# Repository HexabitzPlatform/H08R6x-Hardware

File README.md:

# H01R0x-Hardware
Hexabitz RGB LED Module Hardware Design

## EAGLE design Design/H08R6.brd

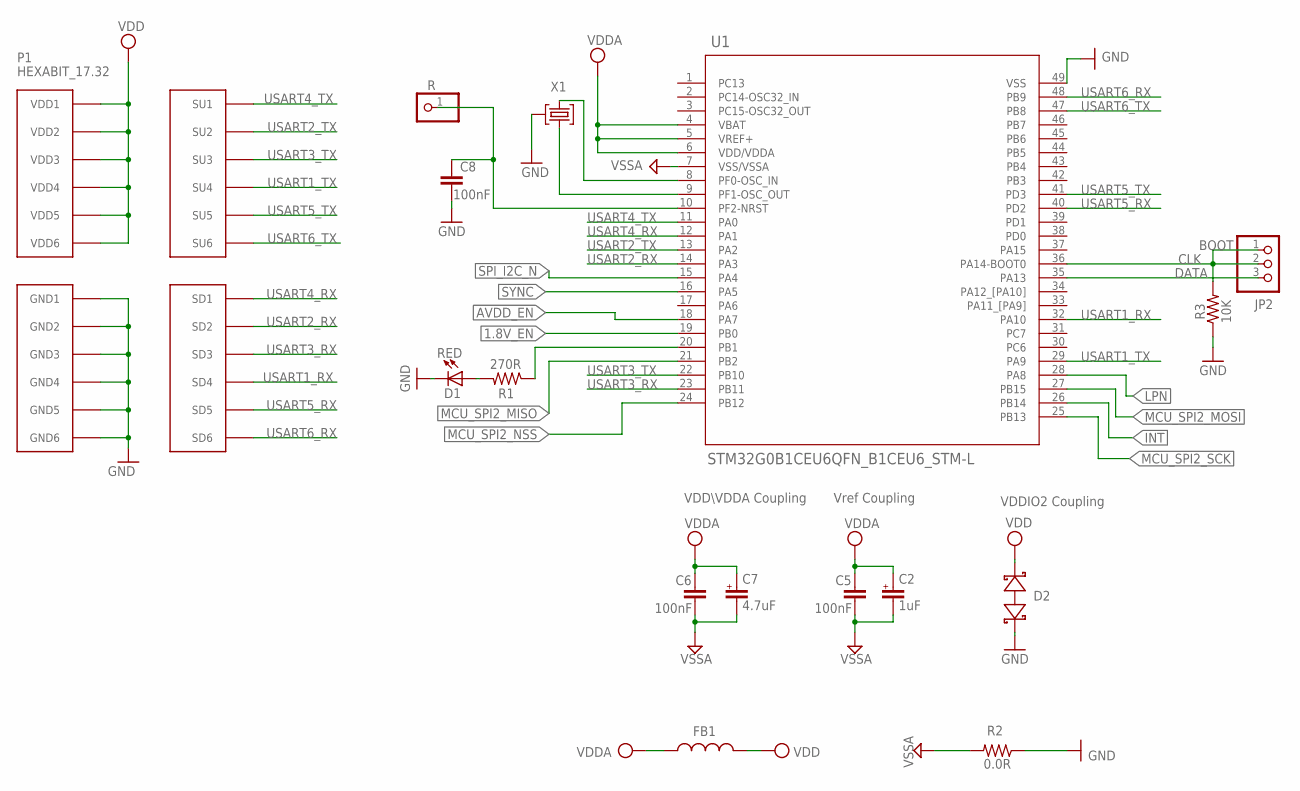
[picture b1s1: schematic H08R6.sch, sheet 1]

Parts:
C2: 1uF; C-0603-POL
C5, C6, C8: 100nF; C-0402
C7: 4.7uF; C-0603-POL
D1: RED; VLMS1300-GS08; MPN VLMS1300-GS08
D2: BOURNS_CDSOD323-T03SCBOURNS_CDSOD323-T03SC_0_0; BOURNS_CDSOD323-T03SC_0
FB1: FB-TDK_MMZ1608Y300B; MPN MMZ1608Y300B
JP2: PINHD-1X3; 1X03
P1: HEXABIT_17.32
R: R; 1X01
R1: 270R; R-0402
R2: 0.0R; R-0402; MPN RC0603JR-070RL
R3: 10K; R-0402
TRIMBLE-LOGO1: HEXA-LOGO
U1: STM32G0B1CEU6QFN_B1CEU6_STM-L; QFN_B1CEU6_STM-L
X1: XTALL_CSTCE8M00G52

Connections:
1.8V_EN: U1.19 (PB0); also elsewhere on the board
AVDD_EN: U1.18 (PA7); also elsewhere on the board
CLK: JP2.1, JP2.2, R3.2, U1.36 (PA14-BOOT0)
DATA: JP2.3, U1.35 (PA13)
GND: C8.2, D1.C, D2.2 (C), P1.PAD_PD7 (GND1), P1.PAD_PD8 (GND2), P1.PAD_PD9 (GND3), P1.PAD_PD10 (GND4), P1.PAD_PD11 (GND5), P1.PAD_PD12 (GND6), R2.1, R3.1, U1.49 (VSS), X1.P$2 (2); also elsewhere on the board
INT: U1.26 (PB14); also elsewhere on the board
LPN: U1.28 (PA8); also elsewhere on the board
MCU_SPI2_MISO: U1.21 (PB2); also elsewhere on the board
MCU_SPI2_MOSI: U1.27 (PB15); also elsewhere on the board
MCU_SPI2_NSS: U1.24 (PB12); also elsewhere on the board
MCU_SPI2_SCK: U1.25 (PB13); also elsewhere on the board
unnamed: D1.A, R1.2
unnamed: C8.1, R.1, U1.10 (PF2-NRST)
unnamed: U1.9 (PF1-OSC_OUT), X1.P$1 (1)
unnamed: U1.8 (PF0-OSC_IN), X1.P$3 (3)
unnamed: R1.1, U1.20 (PB1)
SPI_I2C_N: U1.15 (PA4); also elsewhere on the board
SYNC: U1.16 (PA5); also elsewhere on the board
USART1_RX: P1.PAD_PD4 (SD4), U1.32 (PA10)
USART1_TX: P1.PAD_PU4 (SU4), U1.29 (PA9)
USART2_RX: P1.PAD_PD2 (SD2), U1.14 (PA3)
USART2_TX: P1.PAD_PU2 (SU2), U1.13 (PA2)
USART3_RX: P1.PAD_PD3 (SD3), U1.23 (PB11)
USART3_TX: P1.PAD_PU3 (SU3), U1.22 (PB10)
USART4_RX: P1.PAD_PD1 (SD1), U1.12 (PA1)
USART4_TX: P1.PAD_PU1 (SU1), U1.11 (PA0)
USART5_RX: P1.PAD_PD5 (SD5), U1.40 (PD2)
USART5_TX: P1.PAD_PU5 (SU5), U1.41 (PD3)
USART6_RX: P1.PAD_PD6 (SD6), U1.48 (PB9)
USART6_TX: P1.PAD_PU6 (SU6), U1.47 (PB8)
VDD: D2.1 (A), FB1.2, P1.PAD_PU7 (VDD1), P1.PAD_PU8 (VDD2), P1.PAD_PU9 (VDD3), P1.PAD_PU10 (VDD4), P1.PAD_PU11 (VDD5), P1.PAD_PU12 (VDD6); also elsewhere on the board
VDDA: C2.1, C5.1, C6.1, C7.1, FB1.1, U1.4 (VBAT), U1.5 (VREF+), U1.6 (VDD/VDDA)
VSSA: C2.2, C5.2, C6.2, C7.2, R2.2, U1.7 (VSS/VSSA)

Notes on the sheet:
Vref Coupling
VDDIO2 Coupling
VDD\VDDA Coupling
BOOT

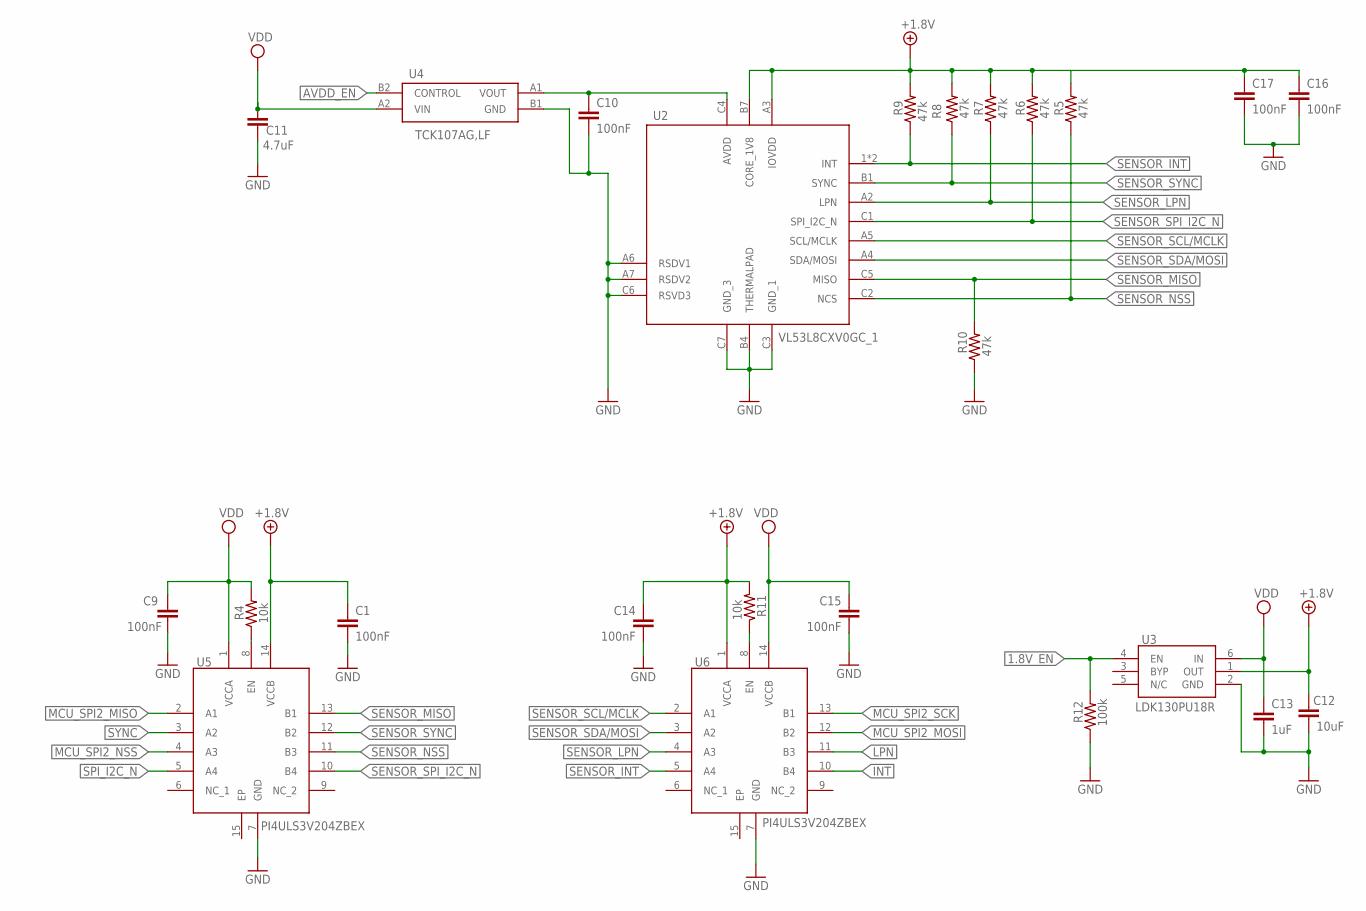
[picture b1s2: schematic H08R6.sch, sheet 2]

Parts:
C1, C9, C10, C14, C15, C16, C17: 100nF; C-0402
C11: 4.7uF; C-0603
C12: 10uF; C-0402
C13: 1uF; C-0402
R4, R11: 10k; R-0402
R5, R6, R7, R8, R9, R10: 47k; R-0402
R12: 100k; R-0402
U2: VL53L8CXV0GC_1; VL53L8CXV0GC1
U3: LDK130PU18R
U4: TCK107AG,LF; BGA4C40P2X2_79X79X59
U5, U6: PI4ULS3V204ZBEX

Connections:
1.8V_EN: R12.2, U3.4 (EN); also elsewhere on the board
+1.8V: C1.1, C12.1, C14.1, C16.1, C17.1, R5.2, R6.2, R7.2, R8.2, R9.2, R11.2, U2.A3 (IOVDD), U2.B7 (CORE_1V8), U3.1 (OUT), U5.14 (VCCB), U6.1 (VCCA)
AVDD_EN: U4.B2 (CONTROL); also elsewhere on the board
CONTROLLED_AVDD: C10.1, U2.C4 (AVDD), U4.A1 (VOUT)
GND: C1.2, C9.2, C10.2, C11.2, C12.2, C13.2, C14.2, C15.2, C16.2, C17.2, R10.1, R12.1, U2.A6 (RSDV1), U2.A7 (RSDV2), U2.B4 (THERMALPAD), U2.C3 (GND_1), U2.C6 (RSVD3), U2.C7 (GND_3), U3.2 (GND), U4.B1 (GND), U5.7 (GND), U6.7 (GND); also elsewhere on the board
INT: U6.10 (B4); also elsewhere on the board
LPN: U6.11 (B3); also elsewhere on the board
MCU_SPI2_MISO: U5.2 (A1); also elsewhere on the board
MCU_SPI2_MOSI: U6.12 (B2); also elsewhere on the board
MCU_SPI2_NSS: U5.4 (A3); also elsewhere on the board
MCU_SPI2_SCK: U6.13 (B1); also elsewhere on the board
unnamed: R4.1, U5.8 (EN)
unnamed: R11.1, U6.8 (EN)
SENSOR_INT: R9.1, U2.1 (INT), U2.A1 (INT), U6.5 (A4)
SENSOR_LPN: R7.1, U2.A2 (LPN), U6.4 (A3)
SENSOR_MISO: R10.2, U2.C5 (MISO), U5.13 (B1)
SENSOR_NSS: R5.1, U2.C2 (NCS), U5.11 (B3)
SENSOR_SCL/MCLK: U2.A5 (SCL/MCLK), U6.2 (A1)
SENSOR_SDA/MOSI: U2.A4 (SDA/MOSI), U6.3 (A2)
SENSOR_SPI_I2C_N: R6.1, U2.C1 (SPI_I2C_N), U5.10 (B4)
SENSOR_SYNC: R8.1, U2.B1 (SYNC), U5.12 (B2)
SPI_I2C_N: U5.5 (A4); also elsewhere on the board
SYNC: U5.3 (A2); also elsewhere on the board
VDD: C9.1, C11.1, C13.1, C15.1, R4.2, U3.6 (IN), U4.A2 (VIN), U5.1 (VCCA), U6.14 (VCCB); also elsewhere on the board

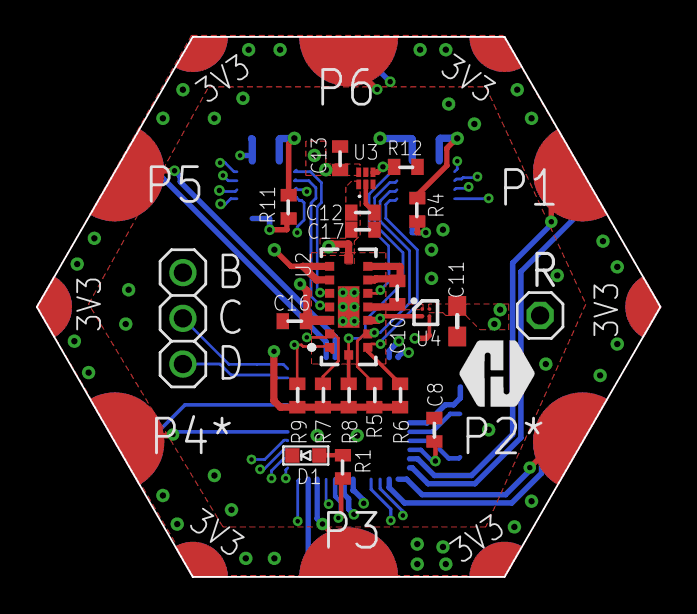
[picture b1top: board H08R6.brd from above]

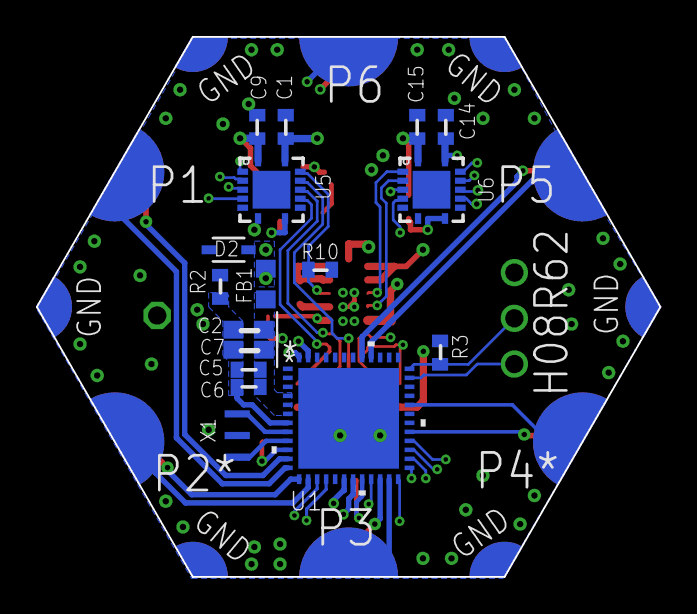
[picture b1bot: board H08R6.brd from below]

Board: 4 copper layers, 34.6 x 30.0 mm, 41 parts (17 on the bottom side), 45 nets.

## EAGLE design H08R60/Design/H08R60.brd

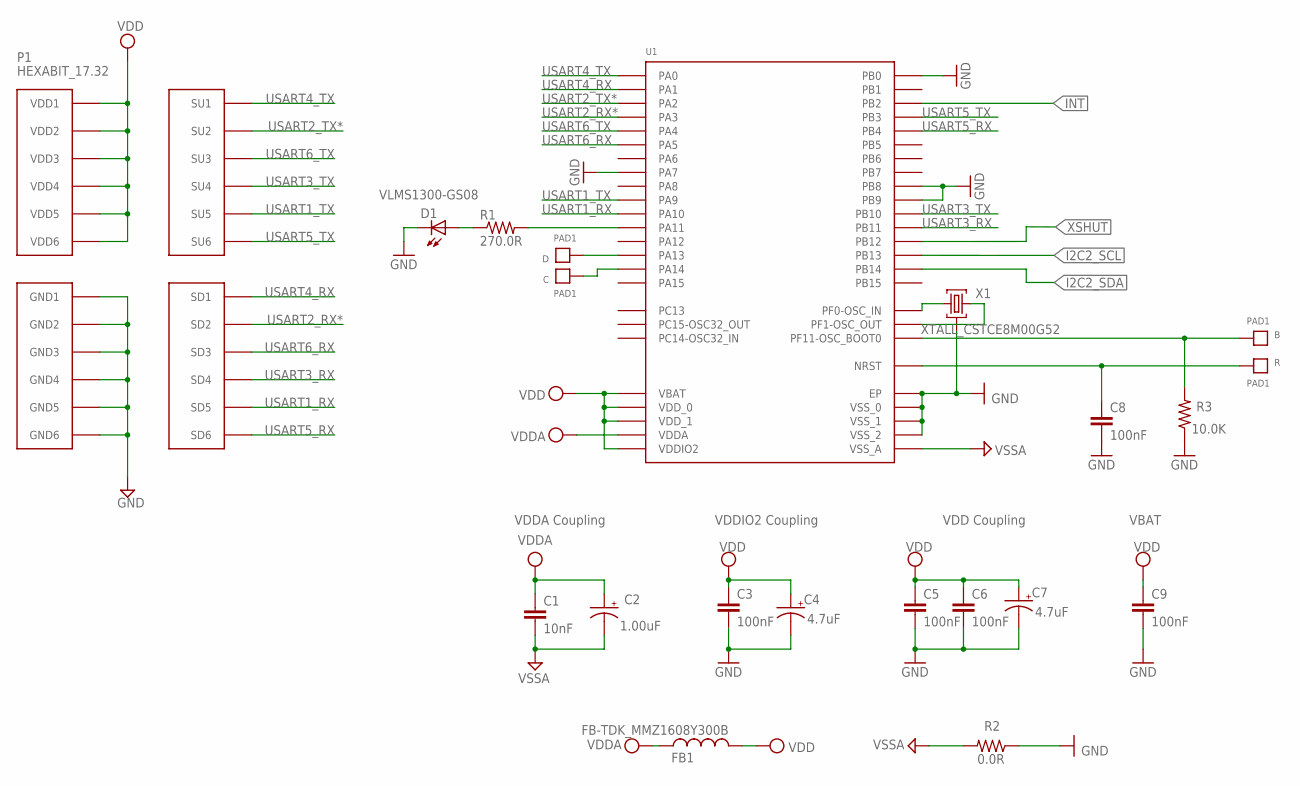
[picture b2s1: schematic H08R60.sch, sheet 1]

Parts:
B: PAD1
C: PAD1
C1: 10nF; C-0603; TOLERANCE 10%; VOLTAGE_RATING 50V; MPN C0603C103K5RACTU
C2: 1.00uF; C-0805; TOLERANCE 10%; VOLTAGE_RATING 16V; MPN CC0805KKX7R7BB105
C3, C6, C8: 100nF; C-0603; TOLERANCE 10%; VOLTAGE_RATING 10V; MPN C0603C104K8RACTU
C4, C7: 4.7uF; C-0805; TOLERANCE 10%; VOLTAGE_RATING 25V; MPN GRM21BC81E475KA12L
C5: 100nF; C-0603; TOLERANCE 10%; VOLTAGE_RATING 10; MPN C0603C104K8RACTU
C9: 100nF; C-0603; TOLERANCE 10V; VOLTAGE_RATING 10%; MPN C0603C104K8RACTU
D: PAD1
D1: VLMS1300-GS08; MPN VLMS1300-GS08
FB1: FB-TDK_MMZ1608Y300B; MPN MMZ1608Y300B
P1: HEXABIT_17.32
R: PAD1
R1: 270.0R; R-0603; TOLERANCE 1%; MPN RC0603FR-07270RL
R2: 0.0R; R-0603; MPN RC0603JR-070RL
R3: 10.0K; R-0603; TOLERANCE 5%; MPN RC0603JR-0710KL
U1: STM32F091CBU6
X1: XTALL_CSTCE8M00G52

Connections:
B1: B.P$1, B.P$2, R3.2, U1.P$44 (PF11-OSC_BOOT0)
GND: C3.2, C4.2 (-), C5.2, C6.2, C7.2 (-), C8.2, C9.2, D1.C, P1.PAD_PD7 (GND1), P1.PAD_PD8 (GND2), P1.PAD_PD9 (GND3), P1.PAD_PD10 (GND4), P1.PAD_PD11 (GND5), P1.PAD_PD12 (GND6), R2.1, R3.1, U1.EP, U1.P$17 (PA7), U1.P$18 (PB0), U1.P$23 (VSS_0), U1.P$35 (VSS_1), U1.P$45 (PB8), U1.P$46 (PB9), U1.P$47 (VSS_2), X1.P$2 (2)
I2C2_SCL: U1.P$26 (PB13); also elsewhere on the board
I2C2_SDA: U1.P$27 (PB14); also elsewhere on the board
INT: U1.P$20 (PB2); also elsewhere on the board
unnamed: R1.2, U1.P$32 (PA11)
unnamed: D1.A, R1.1
unnamed: U1.P$5 (PF0-OSC_IN), X1.P$1 (1)
unnamed: U1.P$6 (PF1-OSC_OUT), X1.P$3 (3)
unnamed: D.P$1, D.P$2, U1.P$34 (PA13)
unnamed: C.P$1, C.P$2, U1.P$37 (PA14)
R1: C8.1, R.P$1, R.P$2, U1.P$7 (NRST)
USART1_RX: P1.PAD_PD5 (SD5), U1.P$31 (PA10)
USART1_TX: P1.PAD_PU5 (SU5), U1.P$30 (PA9)
USART2_RX*: P1.PAD_PD2 (SD2), U1.P$13 (PA3)
USART2_TX*: P1.PAD_PU2 (SU2), U1.P$12 (PA2)
USART3_RX: P1.PAD_PD4 (SD4), U1.P$22 (PB11)
USART3_TX: P1.PAD_PU4 (SU4), U1.P$21 (PB10)
USART4_RX: P1.PAD_PD1 (SD1), U1.P$11 (PA1)
USART4_TX: P1.PAD_PU1 (SU1), U1.P$10 (PA0)
USART5_RX: P1.PAD_PD6 (SD6), U1.P$40 (PB4)
USART5_TX: P1.PAD_PU6 (SU6), U1.P$39 (PB3)
USART6_RX: P1.PAD_PD3 (SD3), U1.P$15 (PA5)
USART6_TX: P1.PAD_PU3 (SU3), U1.P$14 (PA4)
VDD: C3.1, C4.1 (+), C5.1, C6.1, C7.1 (+), C9.1, FB1.2, P1.PAD_PU7 (VDD1), P1.PAD_PU8 (VDD2), P1.PAD_PU9 (VDD3), P1.PAD_PU10 (VDD4), P1.PAD_PU11 (VDD5), P1.PAD_PU12 (VDD6), U1.P$1 (VBAT), U1.P$24 (VDD_0), U1.P$36 (VDDIO2), U1.P$48 (VDD_1); also elsewhere on the board
VDDA: C1.1, C2.1 (+), FB1.1, U1.P$9 (VDDA)
VSSA: C1.2, C2.2 (-), R2.2, U1.P$8 (VSS_A)
XSHUT: U1.P$25 (PB12); also elsewhere on the board

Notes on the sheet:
VDDA Coupling
VDDIO2 Coupling
VDD Coupling
VBAT

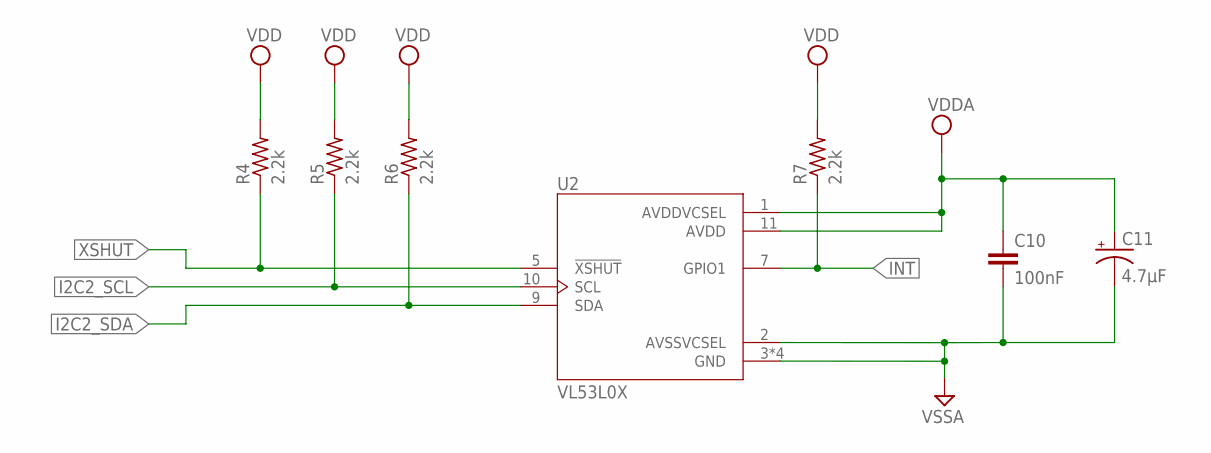
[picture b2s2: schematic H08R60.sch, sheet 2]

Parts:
C10: 100nF; C-0603; TOLERANCE ±10%; VOLTAGE_RATING 16.0 V; MPN C0603C104K8RACTU
C11: 4.7uF; C-0805; TOLERANCE 10%; VOLTAGE_RATING 25V; MPN GRM21BC81E475KA12L
R4, R5, R6, R7: 2.2k; R-0603; TOLERANCE ±1%; MPN RC0603FR-07270RL
U2: VL53L0X; SENSOR_VL53L0X

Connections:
AGND: C10.2, C11.2 (-), U2.2 (AVSSVCSEL), U2.3 (GND), U2.4 (GND), U2.6 (GND), U2.12 (GND)
I2C2_SCL: R5.1, U2.10 (SCL); also elsewhere on the board
I2C2_SDA: R6.1, U2.9 (SDA); also elsewhere on the board
INT: R7.1, U2.7 (GPIO1); also elsewhere on the board
VDD: C10.1, C11.1 (+), R4.2, R5.2, R6.2, R7.2, U2.1 (AVDDVCSEL), U2.11 (AVDD); also elsewhere on the board
XSHUT: R4.1, U2.5 (!XSHUT); also elsewhere on the board

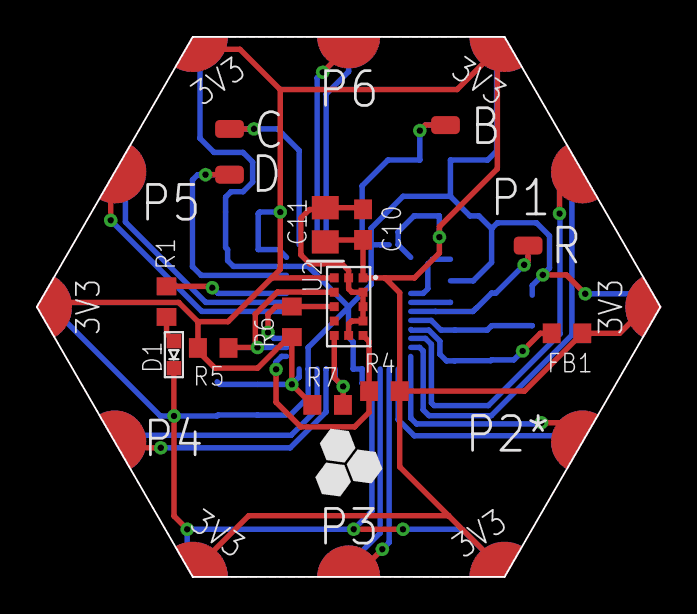
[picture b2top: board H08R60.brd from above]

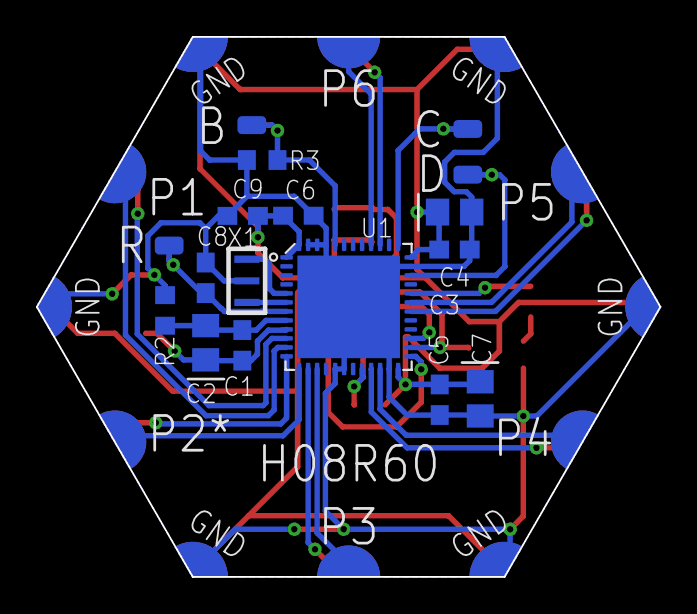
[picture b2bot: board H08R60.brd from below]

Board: 2 copper layers, 34.6 x 30.0 mm, 28 parts (13 on the bottom side), 29 nets.

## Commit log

2019-05-23 First release rev 0
2022-12-21 - Changing the MC to STM32G0 - Editing the electronic design to improve the performance
2022-12-22 Edit README.md file
2023-02-13 -Correcting some documentation issues
2024-01-20 -The final design, all done. -Upgrade the IR sensor and use VL53L8.
2024-01-29 Correct the EN pin of the level shifter IC referencing.
2024-04-04 Update the description
2024-04-30 -Fix missing connection -Add TVS -Update the logo -Fix clearence and soldermask
2024-12-11 -Change the MCU footprint to STM32G0B1CEU6
2024-12-13 Fix BOM
2024-12-26 Add the TVS to the BOM

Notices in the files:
parts and their libraries:
COPYRIGHT: Copyright (C) 2021 Ultra Librarian. All rights reserved.
